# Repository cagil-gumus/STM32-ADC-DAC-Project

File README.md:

# STM32 ADC DAC Project 

The goal is simple. Make a simple PCB with STM32F103C8Tx + ADC + DAC with Audio Analog front end to process raw Guitar pick up signals and drive a simple speaker. 

Following things I want to learn:

* Learn KiCad
* Learn Embedded C -> Implement simple DSP algo on STM32 on a Audio stream
* Learn modern PCB design techniques on mixed design (analog + Digital) 
* Learn aarch64 architecture

I will follow this video: https://www.youtube.com/watch?v=aVUqaB0IMh4

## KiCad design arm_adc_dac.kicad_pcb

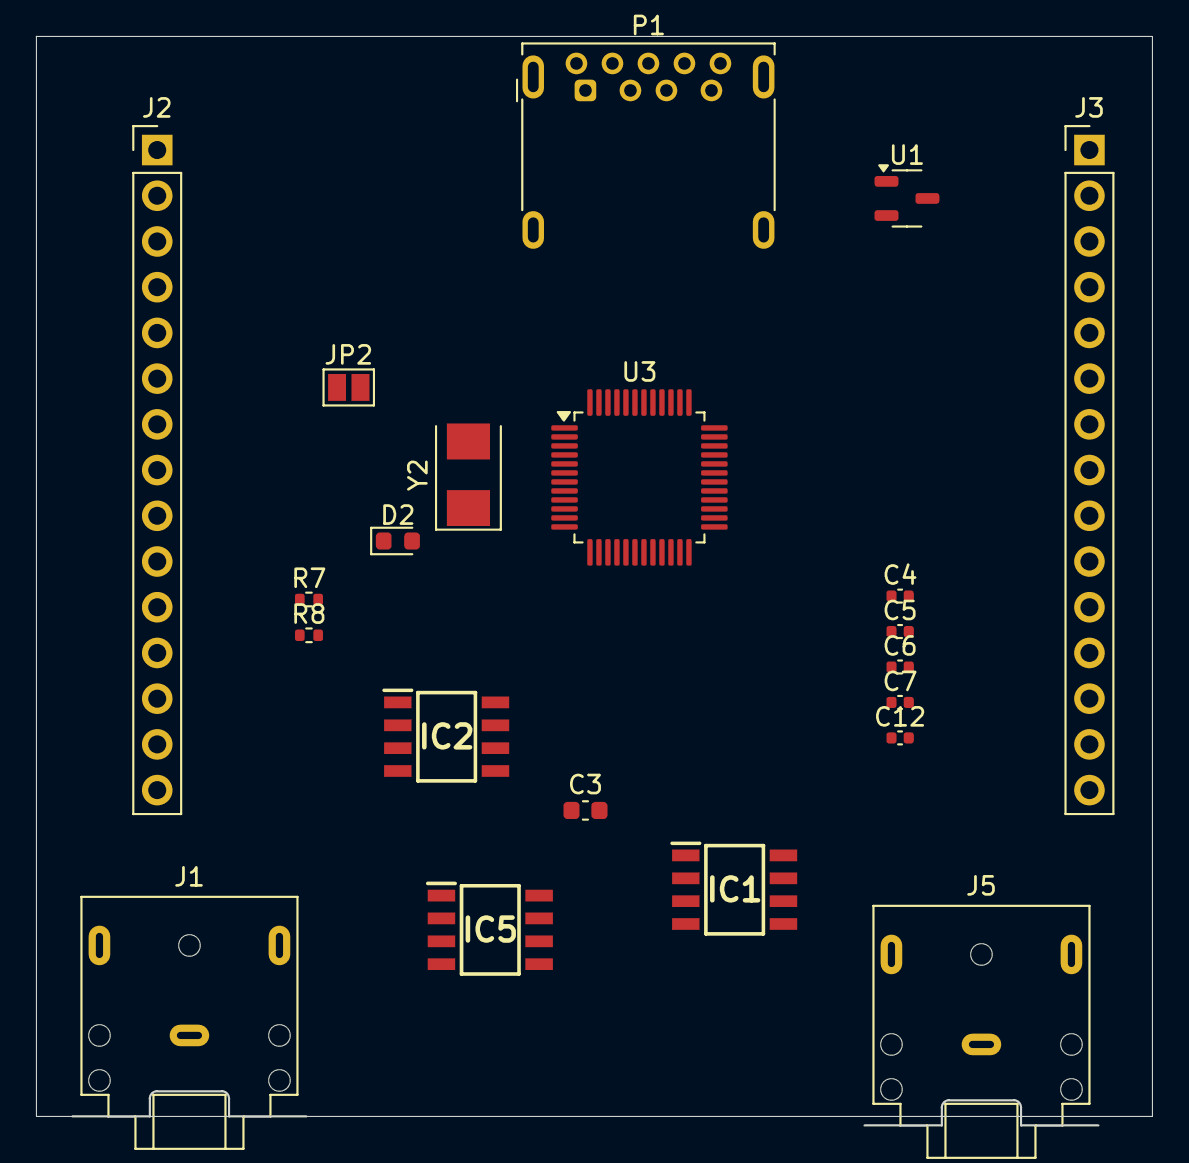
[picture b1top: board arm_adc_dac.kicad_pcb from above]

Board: 2 copper layers, 61.9 x 60.5 mm, 21 parts (0 on the bottom side), 35 nets, no tracks yet.

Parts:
C3: 4u7; C_0603_1608Metric
C4, C5, C6, C7, C12: 100n; C_0402_1005Metric
D2: BLUE; LED_0603_1608Metric
IC1, IC5: OPA134UA_2K5; SOIC127P600X175-8N
IC2: MCP3201-BI_SN; SOIC127P600X175-8N
J1: Input Jack; Jack_3.5mm_CUI_SJ1-3523N_Horizontal
J2, J3: Conn_01x15; PinHeader_1x15_P2.54mm_Vertical
J5: Output Jack; Jack_3.5mm_CUI_SJ1-3523N_Horizontal
JP2: SolderJumper_2_Open; SolderJumper-2_P1.3mm_Open_Pad1.0x1.5mm
P1: USB_C_Plug_USB2.0; USB3_A_Molex_48393-001
R7, R8: 10k; R_0402_1005Metric
U1: XC6206PxxxMR; SOT-23-3
U3: STM32F103C8Tx; LQFP-48_7x7mm_P0.5mm
Y2: 8MHz; Crystal_SMD_5032-2Pin_5.0x3.2mm

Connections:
+3.3V: C3.1, C4.1, C5.1, C6.1, C7.1, C12.2, IC2.8 (VDD), JP2.1 (A), R8.1, U1.2 (VO), U3.1 (VBAT), U3.24 (VDD), U3.36 (VDD), U3.48 (VDD)
+3.3VA: IC1.7 (V+), IC5.7 (V+), U3.9 (VDDA)
/Digital/usb_data_p: R8.2, U3.38 (PA15)
GND: C3.2, C4.2, C5.2, C6.2, C7.2, D2.1 (K), IC1.3 (+IN), IC1.4 (V-), IC2.3 (IN-), IC2.4 (VSS), IC5.3 (+IN), IC5.4 (V-), J1.T, J5.T, R7.2, U1.1 (GND), U3.8 (VSSA), U3.23 (VSS), U3.35 (VSS), U3.47 (VSS)
unnamed: D2.2 (A), U3.33 (PA12)
unnamed: IC5.6 (OUTPUT), J5.S
unnamed: JP2.2 (B), R7.1, U3.44 (BOOT0)
unnamed: U3.5 (PD0), Y2.1
unnamed: U3.6 (PD1), Y2.2
PA0: J3.1, U3.10 (PA0)
PA1: J3.2, U3.11 (PA1)
PA2: J3.3, U3.12 (PA2)
PA8: J3.9, U3.29 (PA8)
PA9: J3.10, U3.30 (PA9)
PA10: J3.11, U3.31 (PA10)
PA11: J3.12, U3.32 (PA11)
PA13: J3.14, U3.34 (PA13)
PB0: J2.1, U3.18 (PB0)
PB1: J2.2, U3.19 (PB1)
PB2: J2.3, U3.20 (PB2)
PB3: J2.4, U3.39 (PB3)
PB4: J2.5, U3.40 (PB4)
PB5: J2.6, U3.41 (PB5)
PB6: J2.7, U3.42 (PB6)
PB7: J2.8, U3.43 (PB7)
PB8: J2.9, U3.45 (PB8)
PB9: J2.10, U3.46 (PB9)
PB10: J2.11, U3.21 (PB10)
PB11: J2.12, U3.22 (PB11)
PB12: J2.13, U3.25 (PB12)
PB13: J2.14, U3.26 (PB13)
PB14: J2.15, U3.27 (PB14)
SPI_CS_N_ADC: IC2.5 (~CS/SHDN), U3.13 (PA3)
SPI_MISO: IC2.6 (DOUT), U3.16 (PA6)
SPI_SCK: IC2.7 (CLK), U3.15 (PA5)

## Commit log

2024-12-28 missing rough plan
2025-01-04 divide the schematic into sub sections, use 12 bit ADC/DAC, add schematic
2025-01-06 extend analog front end section with input buffer and amplification stage, add missing schematics
2025-01-06 update schematic pdf
